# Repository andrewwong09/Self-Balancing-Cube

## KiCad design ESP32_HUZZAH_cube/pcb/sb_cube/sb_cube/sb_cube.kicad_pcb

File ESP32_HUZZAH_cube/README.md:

# Connecting to ESP32 HUZZAH Feather
Inspired by (this aricle)[https://medium.com/@18218004/devlog-6-bluetooth-and-esp32-ba076a8e207d]

After connecting / pairing to device on Ubuntu 22.04, passkey is presented and manually accepted, but device disconnects shortly after; however, remains paired.

*Work around to connect*
```
# 40:91:51:1D:FE:6E is mac address of ESP32, which can be found with "bluetoothctl scan on"
sudo rfcomm connect /dev/rfcomm0 40:91:51:1D:FE:6E 1
sudo rfcomm connect /dev/rfcomm0 0C:DC:7E:CA:DD:36 1

# Send serial command
sudo su -c "echo 0 > /dev/rfcomm0"
```

*Work around to display serial outputs in separate terminal*
```
sudo screen /dev/rfcomm0
```

# Programming the ESP32 HUZZAH Feather
- Use v2.0.17 of esp32 by Espressif as suggested in [this Issue](https://github.com/espressif/arduino-esp32/issues/10309) to avoid `Compilation error: 'ledcSetup' was not declared in this scope ESP32 HUZZAH`.

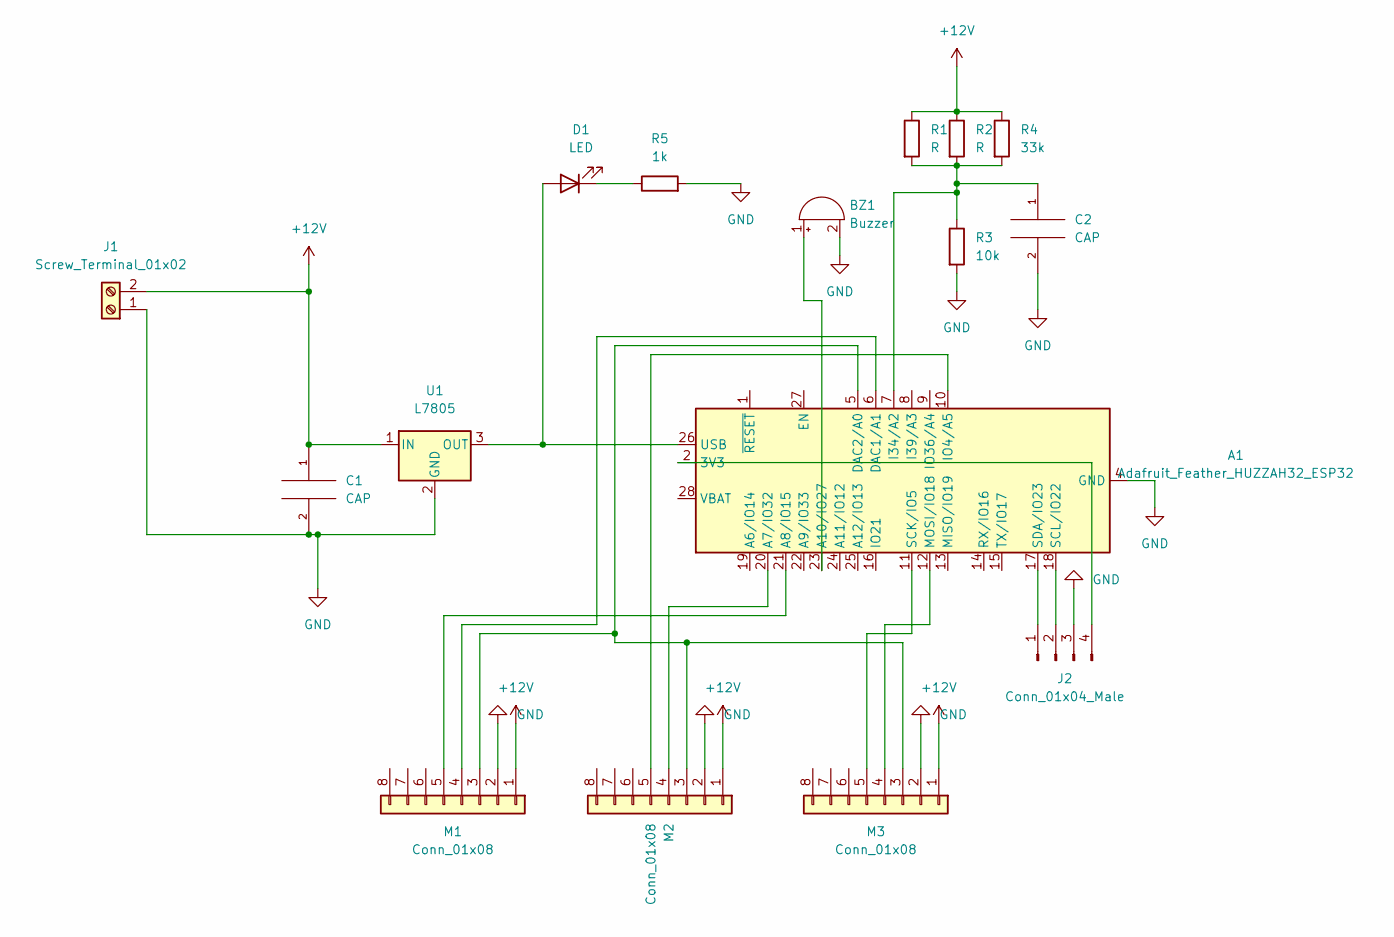
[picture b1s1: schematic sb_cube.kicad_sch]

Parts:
A1: Adafruit_Feather_HUZZAH32_ESP32; Adafruit_Feather
BZ1: Buzzer; Buzzer_12x9.5RM7.6
C1: CAP; CP_Radial_D10.0mm_P5.00mm
C2: CAP; C_Disc_D7.5mm_W2.5mm_P5.00mm
D1: LED; LED_D5.0mm
J1: Screw_Terminal_01x02; TerminalBlock_Altech_AK300-2_P5.00mm
J2: Conn_01x04_Male; PinSocket_1x04_P2.54mm_Vertical
M1, M2, M3: Conn_01x08; PinSocket_1x08_P2.54mm_Vertical
R1, R2: R; R_Axial_DIN0207_L6.3mm_D2.5mm_P7.62mm_Horizontal
R3: 10k; R_Axial_DIN0207_L6.3mm_D2.5mm_P7.62mm_Horizontal
R4: 33k; R_Axial_DIN0207_L6.3mm_D2.5mm_P7.62mm_Horizontal
R5: 1k; R_Axial_DIN0207_L6.3mm_D2.5mm_P7.62mm_Horizontal
U1: L7805; PinSocket_1x03_P2.54mm_Horizontal

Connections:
+12V: C1.1, J1.2, M1.1, M2.1, M3.1, R1.1, R2.1, R4.1, U1.1 (IN)
GND: A1.4 (GND), BZ1.2 (+), C1.2, C2.2, J1.1, J2.3, M1.2, M2.2, M3.2, R3.2, R5.2, U1.2 (GND)
unnamed: A1.2 (3V3), J2.4
unnamed: A1.7 (I34/A2), C2.1, R1.2, R2.2, R3.1, R4.2
unnamed: A1.12 (MOSI/IO18), M3.4
unnamed: A1.17 (SDA/IO23), J2.1
unnamed: A1.18 (SCL/IO22), J2.2
unnamed: A1.20 (A7/IO32), M2.4
unnamed: A1.21 (A8/IO15), M1.5
unnamed: A1.26 (USB), D1.2 (A), U1.3 (OUT)
unnamed: A1.23 (A10/IO27), BZ1.1 (-)
unnamed: D1.1 (K), R5.1
unnamed: A1.6 (DAC1/A1), M1.4
unnamed: A1.10 (IO4/A5), M2.5
unnamed: A1.5 (DAC2/A0), M1.3, M2.3, M3.3
unnamed: A1.11 (SCK/IO5), M3.5

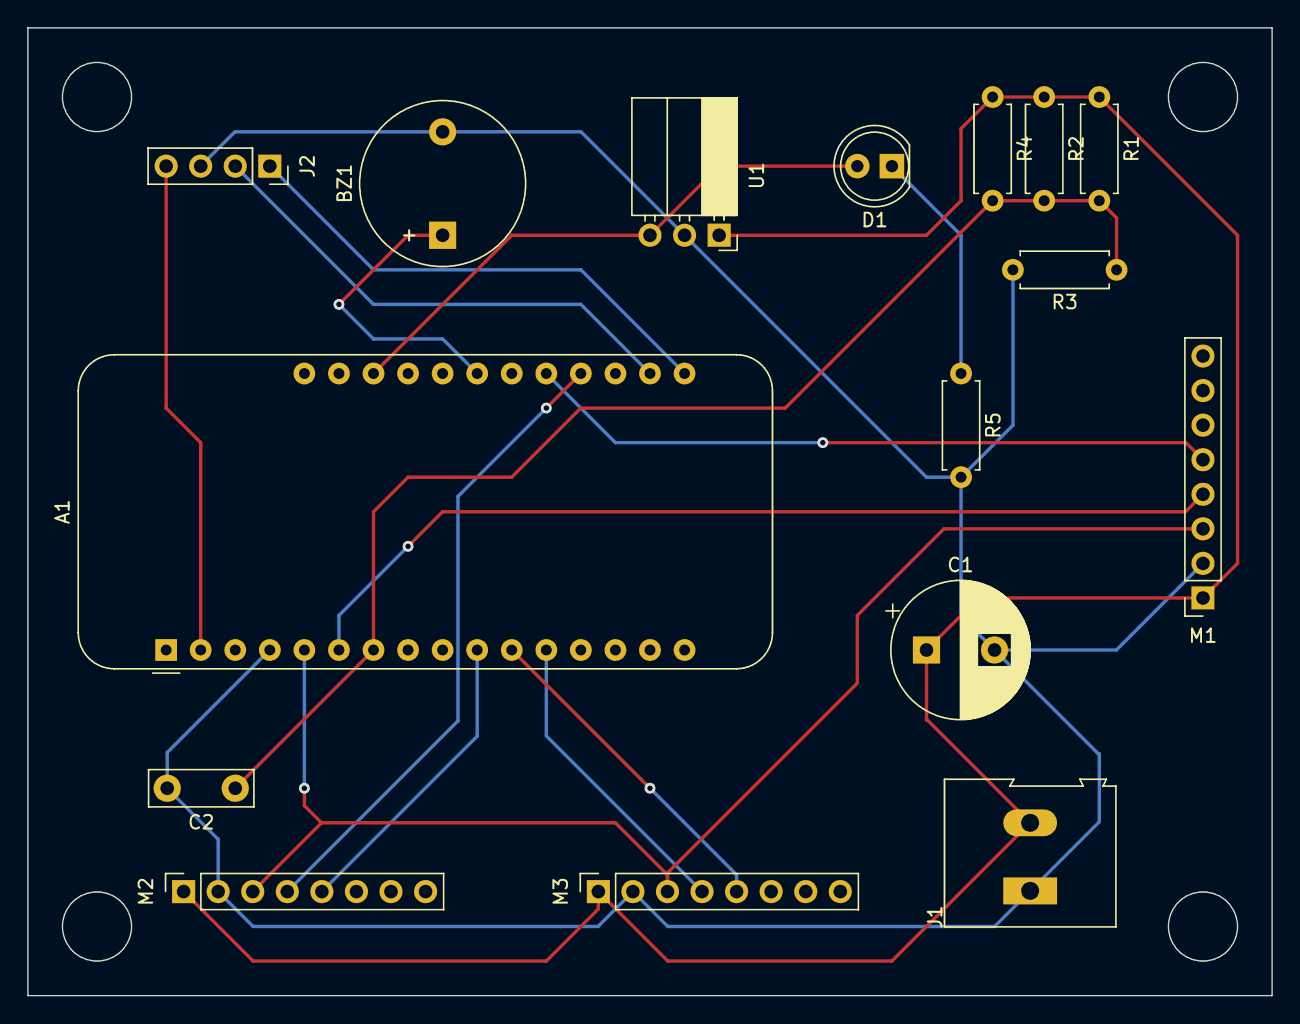
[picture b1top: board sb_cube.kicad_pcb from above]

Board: 2 copper layers, 91.4 x 71.1 mm, 16 parts (0 on the bottom side), 16 nets.

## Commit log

2024-03-19 Added README and copied files for development of ESP32 HUZZAH feather device.
2026-03-14 reoganized arduino code into separate directories. motors_test tests buzzer and does serial prints
2026-03-14 updated README about esp32 library version
2026-03-14 Voltage reading added.
2026-03-14 Fix bug; No extra true in requestFrom, no extra Wire.beginTransmission in the middle.
2026-03-15 v1 pcb
2026-03-16 active to passive buzzer changes
2026-03-16 V2 to pcbway
2026-03-16 updated voltage reader
2026-03-21 another address
